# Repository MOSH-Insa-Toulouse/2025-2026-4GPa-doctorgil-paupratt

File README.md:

# 4A GP - Projet "Du capteur au banc de test" - I4PMH21

## Sommaire

* [Objectif du projet](#objectif-du-projet)
* [Philosophie du projet : Sobriété et Efficacité](#philosophie-du-projet--sobriété-et-efficacité)
* [Livrables](#livrables)
* [LTSpice](#ltspice)
* [KiCad](#kicad)
* [Shield](#shield)
* [Code Arduino](#code-arduino)
* [Application Android](#application-android)
* [Datasheet](#datasheet)
* [Conclusion et Bilan Critique](#conlcusion-et-bilan-critique)

---

## Objectif du projet

Dans le cadre d'un cours dispensé lors du 2<sup>nd</sup> semestre de 4<sup>ème</sup> année de Génie Physique à l'INSA de Toulouse, il nous a été proposé de réaliser un **capteur low-tech à base de graphite**, puis d'en faire une analyse critique argumentée pour en cerner les potentialités mais également pour évoquer des solutions d'amélioration. Ainsi, ce projet nous a permis de balayer l'ensemble du domaine ; du capteur jusqu'à la réalisation d'une **datasheet** et du **banc de test**.

---
## Philosophie du projet : Sobriété et Efficacité
Face à l'urgence climatique et à la demande croissante de systèmes à faible empreinte carbone, ce projet s'inscrit dans une démarche de **sobriété technologique**. Simplifier les composants pour les rendre plus efficaces énergétiquement reste un défi majeur de l'ingénierie moderne.

Si la réalisation de capteurs à haute sensibilité possède une forte valeur ajoutée, il est primordial de questionner nos besoins réels : avons-nous systématiquement besoin d'un capteur ultra-précis s'il consomme davantage ? Ou un capteur plus simple, adapté à l'usage final, est-il suffisant ?

Le choix d'un **capteur graphite "low-tech"** illustre ce compromis (trade-off) entre précision et consommation. Plutôt que de viser la performance absolue au prix d'une complexité accrue, nous avons privilégié une solution optimisée, cohérente avec les ressources disponibles et les exigences réelles du cahier des charges.

---

## Livrables

L'ensemble du projet comprend les éléments suivants :

* **Un shield PCB** branché à une board **Arduino UNO** sur lequel nous retrouverons différents composants tels que :
    * Un capteur graphite
    * Un circuit d'amplification transimpédance
    * Un module Bluetooth
    * Un encodeur rotatoire
    * Un potentiomètre digital (*qui vient remplacer la résistance R2 du circuit d'amplification*)
    * Un capteur de contrainte commercial
* **Une simulation LTSpice** du circuit transimpédance
* **Un fichier KiCad** du shield avec l'ensemble des composants cités en amont
* **Un code Arduino** qui gère le fonctionnement et les communications des modules avec la board
* **Un fichier APK Android** (conçue à l'aide du site *MIT APP Inventor*) qui permet, à partir d'un smartphone Android, de gérer l'interface avec le shield Arduino UNO par le biais d'une communication Bluetooth
* **La datasheet** du capteur graphite

> [!TIP]
> **Conseil de lecture** : Pour une compréhension optimale du projet, commencez par consulter la **Datasheet** qui résume les performances théoriques avant d'explorer les fichiers de conception KiCad.
---

## LTSpice

Afin de valider la faisabilité du projet et d'anticiper le comportement dynamique de notre système, nous avons simulé la chaîne de conditionnement sous LTSpice. Le défi majeur réside dans l'impédance extrêmement élevée du capteur (de l'ordre du $G\Omega$), qui génère des courants infimes, de l'ordre du nanoampère ($nA$). Pour rendre ce signal exploitable par un microcontrôleur, il est impératif de le filtrer contre les bruits parasites et de l'amplifier de manière significative. Le montage de transimpédance présenté ci-dessous remplit cette fonction critique :

*Circuit d'amplification/atténuation*

*Modélisation du capteur*

Ce montage se compose de trois filtres passe-bas distincts pour optimiser le rapport signal/bruit :

* **Premier étage ($R_5, C_1, R_1$)** : Filtre les bruits en courant sur le signal d'entrée induits par l'alimentation 5V (symbolisée par 'SINE' + $C_3$).
* **Deuxième étage ($C_4, R_3$)** : Réduit spécifiquement la composante de bruit à **50 Hz** induite par le réseau électrique ambiant.
* **Troisième étage ($R_6, C_2$)** : Placé en sortie de l'amplificateur, il atténue le bruit thermique et intrinsèque du circuit.

*Atténuation d'environ 46 dB à 50 Hz. Le comportement global du circuit est bel est bien passe-bas.*

Pour extraire la valeur de la résistance du capteur $R_c$ à partir de la tension mesurée $V_{adc}$, nous avons modélisé le circuit en régime statique (Basse Fréquence). 

En considérant l'AOP comme idéal en régime linéaire ($V_+ = V_-$) et en appliquant le théorème de **Millman**, nous obtenons les relations suivantes :

- #### Expression de $V_+$ (Diviseur de tension)
    $$V_+ = \frac{R_1}{R_c + R_1 + R_5} \cdot V_{cc}$$

- #### Expression de $V_-$ (Théorème de Millman)
    Comme l'entrée est reliée à la masse via $R_2$ :

    $$V_- = \frac{\frac{V_{out}}{R_3} + \frac{0}{R_2}}{\frac{1}{R_3} + \frac{1}{R_2}} = V_+$$

- #### Équation finale de la résistance $R_c$
    En posant $V_{out} = V_{adc}$ et en isolant $R_c$, nous arrivons à la formule de transfert utilisée dans le code Arduino :

    $$R_c = R_1 \cdot \frac{V_{cc}}{V_{adc}} \cdot \left(1 + \frac{R_3}{R_2}\right) - R_1 - R_5$$

Cette équation permet au microcontrôleur de convertir en temps réel la tension lue sur la broche analogique en une valeur de résistance physique exploitable pour la datasheet.

### Analyse des simulations et dimensionnement

La simulation nous a permis d'optimiser deux paramètres critiques : le filtrage du bruit secteur et la dynamique de mesure.

#### 1. Optimisation du filtrage (C4 et R3)
L'étude fréquentielle montre l'impact direct des composants sur la qualité du signal :
* **Fréquence de coupure** : Plus $C_4$ est petit, plus la fréquence de coupure $f_c = \frac{1}{2\pi R_3 C_4}$ est élevée, ce qui réduit l'efficacité du filtrage des parasites à **50 Hz**.
* **Gain du filtre** : La résistance $R_2$ permet d'ajuster le décalage vertical du signal pour l'adapter à la fenêtre de lecture.

*Simulation de l'influence de C4 et R3 sur la stabilisation du signal.*

#### 2. Stratégie de Calibration et Plage Dynamique
Pour éviter la saturation de l'ADC de l'Arduino (limité à 5V), nous avons conçu un système de réglage de gain flexible :

* **Problématique** : La résistance des capteurs graphite varie énormément selon le dépôt. Un courant $I_{sens}$ trop élevé peut saturer l'amplificateur à 5V, rendant toute variation de pression invisible.
* **Solution Manuelle** : L'utilisateur peut ajuster dynamiquement le gain via le **potentiomètre numérique** en utilisant l'**encodeur rotatif**. 
* **Objectif** : L'utilisateur tourne l'encodeur pour ramener le signal au repos vers **2,5V** (valeur brute de 512 sur l'ADC). Cela place le point de fonctionnement au milieu de l'échelle de mesure, offrant une marge de manœuvre maximale pour observer les variations sans écrêtage.

---
## KiCad

### Conception du Shield

Afin de concevoir un **shield PCB** conforme au cahier des charges de l'UF **I4PMH21**, nous avons développé un prototype virtuel sous **KiCad**. Cette phase de conception a permis d'intégrer l'ensemble des contraintes électroniques, mécaniques et physiques liées aux composants utilisés.

La première étape a consisté à élaborer la **saisie de schéma** (*schematic*) regroupant l'intégralité des modules :

### Routage du PCB (Layout)

Une fois le schéma validé, nous avons procédé au **routage du PCB**. L'enjeu principal a été la gestion de l'intégrité du signal dans un environnement mixte (analogique/numérique) :

* **Plan de masse** : Mise en place d'un plan de masse continu pour minimiser l'inductance de boucle et assurer une référence stable.
* **Isolation** : Séparation physique des pistes à haute impédance (liées au capteur graphite) pour limiter les couplages capacitifs.
* **Contraintes mécaniques** : Alignement des connecteurs pour un embrochage parfait sur l'Arduino UNO.

Pour maintenir l'intégrité du plan de masse et respecter les contraintes d'espace, nous avons opté pour la mise en place d'un **strap externe (jumper)**. Cette solution a permis de finaliser les connexions tout en garantissant une isolation optimale entre les pistes critiques.

Le design final du shield est présenté ci-dessous :

### Rendu 3D du Shield

Nous avons généré un rendu 3D du PCB pour visualiser l'encombrement final et l'agencement des composants. Voici une vue de dessus du projet :

> [!NOTE]
> **Ajustement des modèles 3D** : Vous remarquerez peut-être des chevauchements visuels sur le rendu. Cela s'explique par l'usage de modèles CAO (fichiers `.step`) standards dont l'encombrement diffère légèrement des composants réels soudés sur le banc de test. L'empreinte au sol (*footprint*) sur le cuivre est cependant parfaitement conforme aux composants physiques.

## Shield
Une fois la conception validée, nous avons procédé à la fabrication physique du shield sur une plaque d'époxy cuivrée à l'aide de Mme. Catherine Crouzet. Le processus de prototypage rapide a suivi les étapes classiques de la photogravure :

* **Insolation** : Transfert du typon (généré sous KiCad) sur la plaque photosensible via une exposition aux UV.

* **Révélation** : Élimination de la résine non exposée à l'aide d'un révélateur chimique.

* **Gravure** : Passage dans une solution de perchlorure de fer pour dissoudre le cuivre non protégé et révéler les pistes.

Après le nettoyage de la carte, nous avons procédé à l'assemblage. Cette étape a nécessité une grande précision, notamment pour le perçage des vias et le soudage des composants traversants (THT) et CMS, en veillant scrupuleusement au respect des contraintes de température pour ne pas endommager le capteur graphite.

> [!WARNING]
> **Points de vigilance (Soudure)** : Lors de l'assemblage, une attention extrême doit être portée à la qualité des soudures. Des micro-courts-circuits ou des contacts intermittents ("soudures sèches") ont été identifiés lors de nos tests initiaux, perturbant la stabilité du signal. Un nettoyage rigoureux et une vérification systématique au multimètre sont indispensables.

> [!NOTE]
> **Évolution du projet (Servomoteur)** : Bien que prévu initialement dans la conception du shield, le servomoteur n'a finalement pas été implémenté. Ce choix s'explique par des contraintes de temps et par le fait que le banc de test s'est révélé parfaitement fonctionnel et suffisant sans le servo pour valider les mesures du capteur.

## Code Arduino

En parallèle de la partie *KiCad*, nous avons développé le [Code Arduino](./Arduino/Code/ProjetMosh/ProjetMosh.ino) permettant la communication des composants avec l'**Arduino UNO**, voici les fonctionnalités principales :

* **Acquisition Analogique** : Lecture haute impédance et conversion du signal en résistance.
* **Contrôle du Gain via Encodeur** : Utilisation de l'**encodeur rotatif** pour incrémenter ou décrémenter la valeur du potentiomètre numérique. Cette interface permet à l'utilisateur de calibrer manuellement le capteur en temps réel.
* **Gestion du Potentiomètre Digital** : Communication via le bus I2C pour mettre à jour la résistance de contre-réaction ($R_2/R_g$) dès qu'une rotation de l'encodeur est détectée.
* **Interface Bluetooth** : Transmission des données vers l'application Android pour un monitoring sans fil.

> [!TIP]
> **Structure du code** : Le code est organisé de manière non-bloquante (utilisation de `millis()` au lieu de `delay()`) pour garantir une réactivité maximale de la liaison Bluetooth et de l'encodeur.

---

## Application Android
Nous avons réalisé une application mobile à l'aide de **MIT App Inventor**.  Ce dashboard permet non seulement de lire les valeurs du capteur graphite en temps réel, mais constitue également un outil d'acquisition de données complet.

> Le code de programmation est disponibles ici : **[Accéder au code de l'application](./Application/Code%20apk)**.

* **Liaison Bluetooth** : Connexion simplifiée avec le module HC-05 présent sur le shield.
* **Graphique Dynamique** : Visualisation temporelle de la résistance pour identifier la sensibilité du capteur à la déformation.

*Interface utilisateur pour la visualisation des données en temps réel.*

---
## Datasheet

La rédaction de la **datasheet** repose sur une série de mesures expérimentales effectuées grâce à un banc de test dédié.

Le banc de test, imprimé en 3D, utilise 7 demi-disques (Ø 1cm à 5cm) pour simuler des déformations contrôlées. Nous avons testé une gamme de capteurs allant du **2H au 3B** pour identifier le meilleur compromis entre conductivité initiale et sensibilité à la flexion.

*Classification des nuances de graphite : de la mine dure (H) à la mine tendre (B).*

*Montage complet*

 **Documentation technique** : Le rapport complet des performances est disponible ici : 
> 📄 **[Consulter la Datasheet (PDF)](./Caractérisation%20et%20Datasheet/Datasheet.pdf)**

> [!NOTE]
> **Sélection des échantillons** : Certains capteurs présentant des valeurs aberrantes ou une instabilité trop marquée ont été écartés de l'analyse finale afin de garantir la cohérence des courbes de tendance.

> [!WARNING]
> **Limites expérimentales** : La reproductibilité des mesures s'est avérée délicate. Plusieurs facteurs ont influencé les résultats :
> * **Variation de densité** du graphite lors du dépôt manuel.
> * **Dégradation mécanique** de la couche de graphite au fil des tests.
> * **Contacts électriques** instables en fin de série.

## Conclusion et Bilan Critique

Ce projet constitue une preuve de concept réussie : il démontre qu’un matériau aussi rudimentaire que le graphite déposé sur papier peut être transformé en un **capteur de déformation (strain sensor)** fonctionnel grâce à une chaîne de conditionnement électronique optimisée.

### Synthèse des résultats
Nos simulations et tests physiques ont validé la réponse piézorésistive attendue : la résistance augmente en extension et diminue en compression. Le système complet (Capteur -> Shield -> Arduino -> Android) est pleinement opérationnel pour du monitoring en temps réel.

Cependant, la reproductibilité demeure le principal défi technologique. L’hétérogénéité du dépôt manuel de graphite et les aléas liés au prototypage artisanal du PCB (gravure chimique, perçage et soudures) limitent la fiabilité des mesures.

### Perspectives : La force du Low-Tech
L'intérêt majeur de ce projet réside dans sa **valeur pédagogique**. Il prouve qu'un système d'instrumentation complet peut être conçu avec des ressources limitées. Plutôt que de complexifier le capteur, l'enjeu futur serait de rendre le processus de dépôt du graphite plus robuste et automatisé.

**En conclusion**, ce projet nous a permis d'appréhender l'ensemble du cycle de vie d'un produit électronique, de la physique fondamentale du capteur jusqu'à l'interface utilisateur mobile.

---
## Remerciements

Nous tenons à remercier Mme. Crouzet et M. Grisolia pour leur encadrement précieux et leurs conseils techniques lors de la phase de conception et de fabrication tout au long de ce projet.

---

## Contact

Si vous avez des questions concernant ce projet ou l'utilisation du shield, n'hésitez pas à nous contacter :

* **Oscar GIL** : [gil-lamassou@insa-toulouse.fr](mailto:gil-lamassou@insa-toulouse.fr)
* **Pau PRAT** : [prat-i-meler@insa-toulouse.fr](mailto:prat-i-meler@insa-toulouse.fr)

---

[↑ Retour au sommaire](#sommaire)

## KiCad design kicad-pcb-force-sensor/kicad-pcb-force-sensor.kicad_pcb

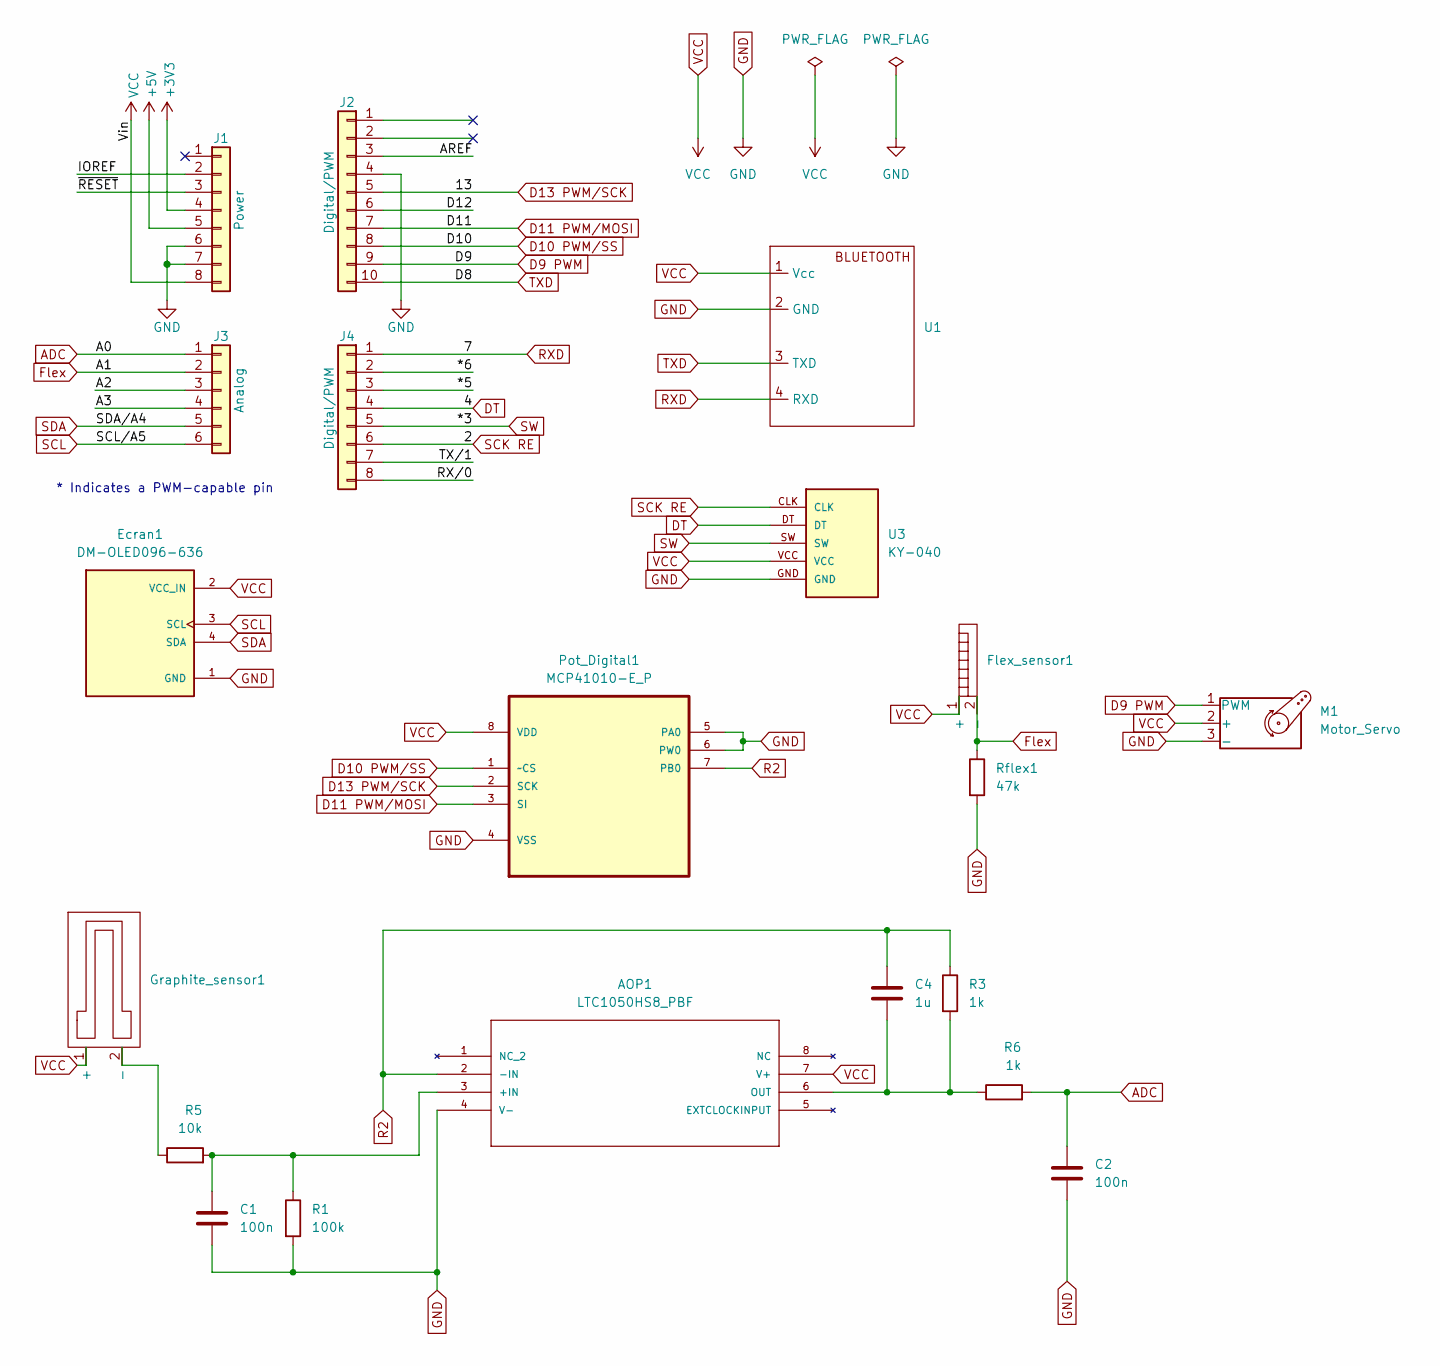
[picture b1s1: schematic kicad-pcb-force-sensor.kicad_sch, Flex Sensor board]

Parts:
AOP1: LTC1050HS8_PBF
C1, C2: 100n; C_Disc_D3.8mm_W2.6mm_P2.50mm
C4: 1u; C_Rect_L9.0mm_W2.5mm_P7.50mm_MKT
Ecran1: DM-OLED096-636; MODULE_DM-OLED096-636
Flex_sensor1: Flex
Graphite_sensor1: Graphite_sensor_emprunt
J1: Power; PinSocket_1x08_P2.54mm_Vertical
J2: Digital/PWM; PinSocket_1x10_P2.54mm_Vertical
J3: Analog; PinSocket_1x06_P2.54mm_Vertical
J4: Digital/PWM; PinSocket_1x08_P2.54mm_Vertical
M1: Motor_Servo; Servo
Pot_Digital1: MCP41010-E_P; MCP41010
R1: 100k; R_Axial_DIN0207_L6.3mm_D2.5mm_P15.24mm_Horizontal
R3, R6: 1k; R_Axial_DIN0204_L3.6mm_D1.6mm_P7.62mm_Horizontal
R5: 10k; R_Axial_DIN0207_L6.3mm_D2.5mm_P10.16mm_Horizontal
Rflex1: 47k; R_Axial_DIN0207_L6.3mm_D2.5mm_P10.16mm_Horizontal
U1: BT_HC05
U3: KY-040; KY-040-PORT

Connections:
+3V3: J1.4
+5V: J1.5
/*5: J4.3
/*6: J4.2
/A2: J3.3
/A3: J3.4
/AREF: J2.3
/D12: J2.6
/IOREF: J1.2
/RX/0: J4.8
/TX/1: J4.7
/~RESET: J1.3
ADC: C2.2, J3.1, R6.2
D9 PWM: J2.9, M1.1 (PWM)
D10 PWM/SS: J2.8, Pot_Digital1.1 (~CS)
D11 PWM/MOSI: J2.7, Pot_Digital1.3 (SI)
D13 PWM/SCK: J2.5, Pot_Digital1.2 (SCK)
DT: J4.4, U3.DT
Flex: Flex_sensor1.2 (-), J3.2, Rflex1.1
GND: AOP1.4 (V-), C1.1, C2.1, Ecran1.1 (GND), J1.6, J1.7, J2.4, M1.3 (-), Pot_Digital1.4 (VSS), Pot_Digital1.5 (PA0), Pot_Digital1.6 (PW0), R1.2, Rflex1.2, U1.2 (GND), U3.GND
unnamed: AOP1.3 (+IN), C1.2, R1.1, R5.2
unnamed: AOP1.6 (OUT), C4.1, R3.2, R6.1
unnamed: Graphite_sensor1.2 (-), R5.1
R2: AOP1.2 (-IN), C4.2, Pot_Digital1.7 (PB0), R3.1
RXD: J4.1, U1.4 (RXD)
SCK RE: J4.6, U3.CLK
SCL: Ecran1.3 (SCL), J3.6
SDA: Ecran1.4 (SDA), J3.5
SW: J4.5, U3.SW
TXD: J2.10, U1.3 (TXD)
VCC: AOP1.7 (V+), Ecran1.2 (VCC_IN), Flex_sensor1.1 (+), Graphite_sensor1.1 (+), J1.8, M1.2 (+), Pot_Digital1.8 (VDD), U1.1 (Vcc), U3.VCC

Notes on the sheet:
* Indicates a PWM-capable pin

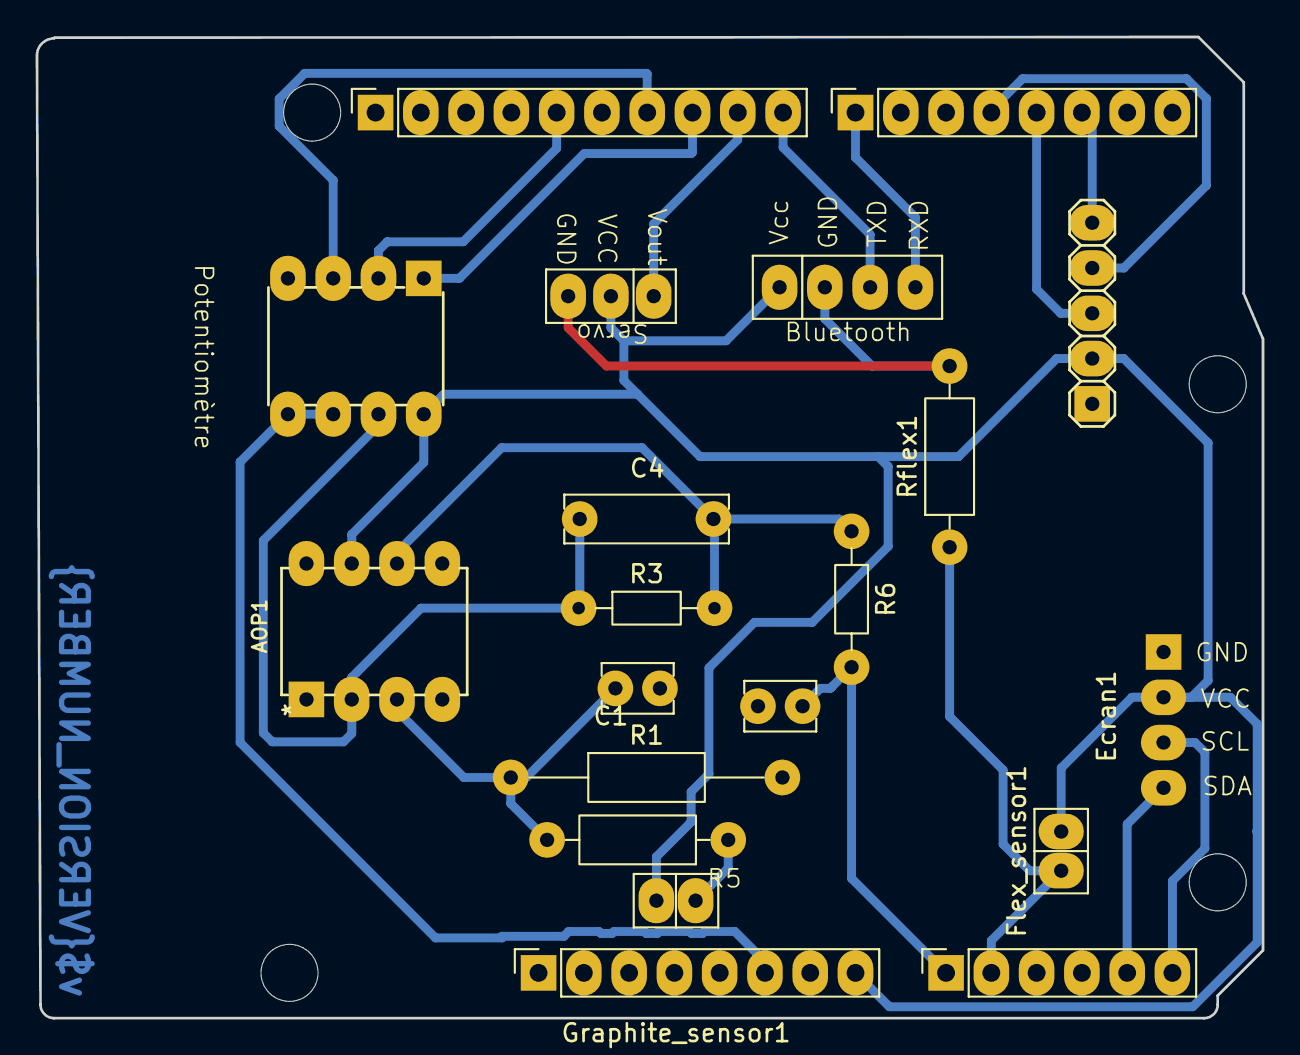
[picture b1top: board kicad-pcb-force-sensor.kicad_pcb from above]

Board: 2 copper layers, 68.8 x 55.0 mm, 24 parts (0 on the bottom side), 19 nets.

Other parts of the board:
MH1, MH2, MH3, MH4: MountingHole_3.2mm

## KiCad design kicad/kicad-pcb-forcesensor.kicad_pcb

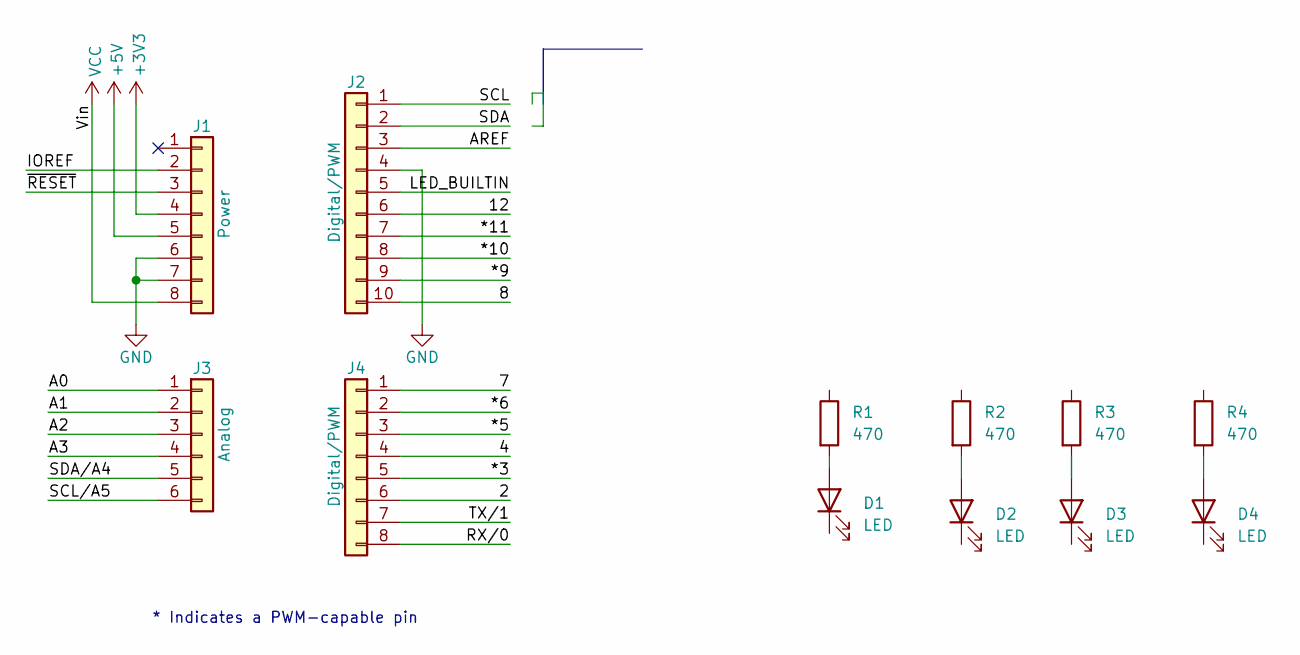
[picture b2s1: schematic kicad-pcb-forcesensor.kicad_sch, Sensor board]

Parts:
D1, D2, D3, D4: LED; LED_D5.0mm
J1: Power; PinSocket_1x08_P2.54mm_Vertical
J2: Digital/PWM; PinSocket_1x10_P2.54mm_Vertical
J3: Analog; PinSocket_1x06_P2.54mm_Vertical
J4: Digital/PWM; PinSocket_1x08_P2.54mm_Vertical
R1, R2, R3, R4: 470; R_Axial_DIN0207_L6.3mm_D2.5mm_P10.16mm_Horizontal

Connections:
+3V3: J1.4
+5V: J1.5
/2: J4.6
/4: J4.4
/7: J4.1
/8: J2.10
/12: J2.6
/*3: J4.5
/*5: J4.3
/*6: J4.2
/*9: J2.9
/*10: J2.8
/*11: J2.7
/A0: J3.1
/A1: J3.2
/A2: J3.3
/A3: J3.4
/AREF: J2.3
/IOREF: J1.2
/LED_BUILTIN: J2.5
/RX/0: J4.8
/SCL: J2.1
/SCL/A5: J3.6
/SDA: J2.2
/SDA/A4: J3.5
/TX/1: J4.7
/~RESET: J1.3
GND: J1.6, J1.7, J2.4
unnamed: D1.2 (A), R1.2
unnamed: D2.2 (A), R2.2
unnamed: D3.2 (A), R3.2
unnamed: D4.2 (A), R4.2
VCC: J1.8

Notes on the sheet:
* Indicates a PWM-capable pin

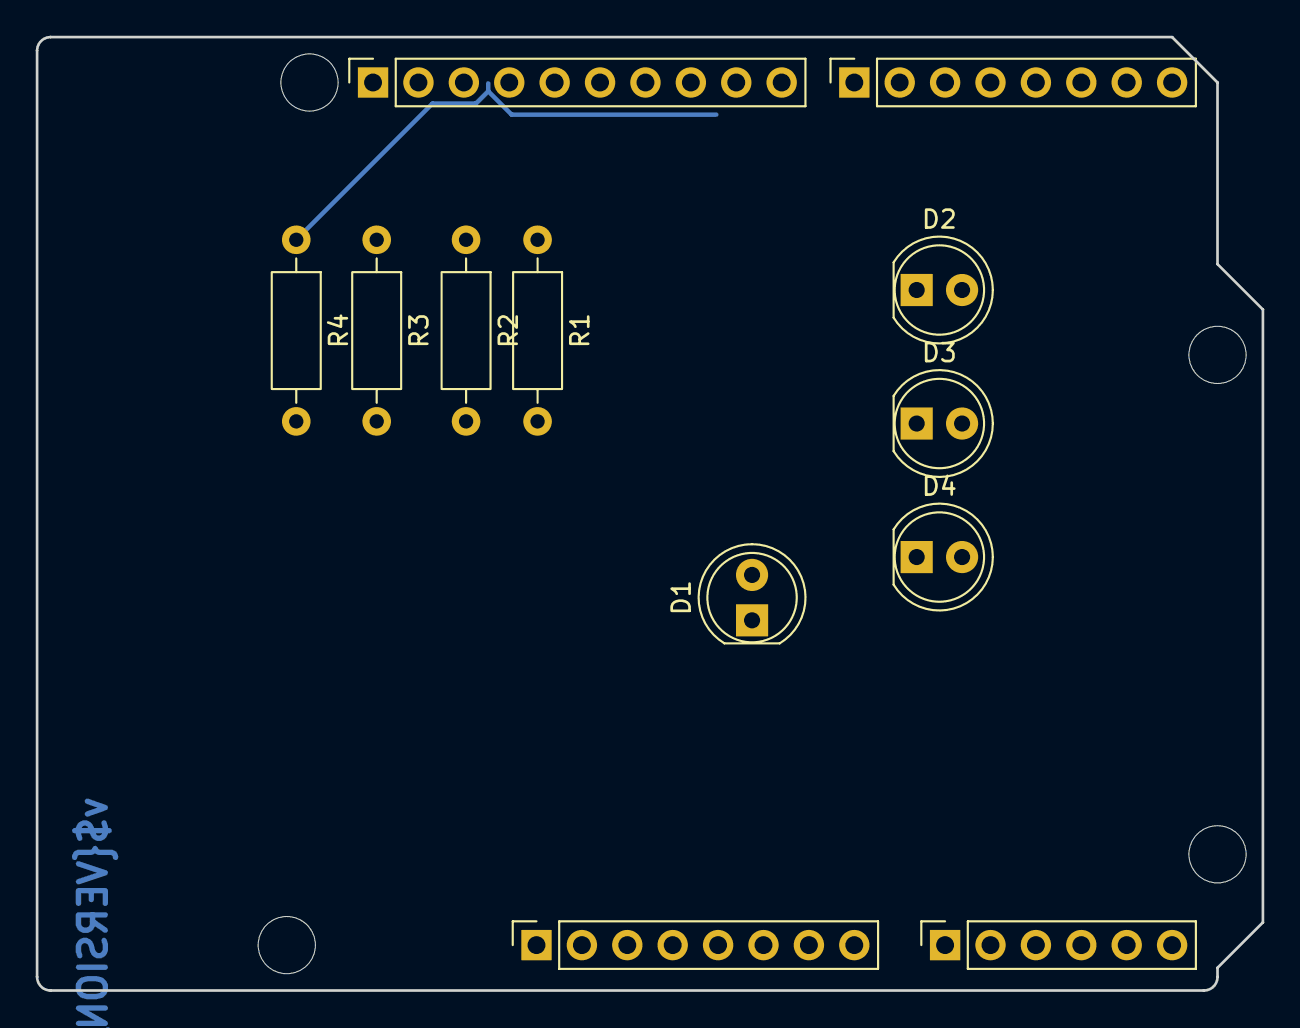
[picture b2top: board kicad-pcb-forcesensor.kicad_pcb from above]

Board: 2 copper layers, 68.6 x 53.3 mm, 16 parts (0 on the bottom side), 5 nets.

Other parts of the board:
MH1, MH2, MH3, MH4: MountingHole_3.2mm

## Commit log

2026-02-18 Ajout du projet KICAD
2026-02-18 Cambio de pin prueba
2026-02-18 prueba
2026-02-18 tamere
2026-02-18 Pines graphic sesor
2026-02-18 ground
2026-02-18 flex_sensor
2026-02-18 prueba2
2026-02-18 Servo
2026-02-18 Ground y VCC
2026-02-18 Avec pistes
2026-02-25 Modifier pins à 0.8mm plus détails
2026-03-10 GND y pins header arduino
2026-04-11 Code Arduino + Primera modificación codigo readme
2026-04-11 update readme 1
2026-04-11 update readme 2
2026-04-11 Update readme partie LTSpice
2026-04-11 Tips
2026-04-11 tips 1
2026-04-13 partie Kicad
2026-04-13 shield
2026-04-13 note évolution du projet servomoteur
2026-04-13 iamge
2026-04-15 Caractérisation et datasheet
2026-04-15 move readme
2026-04-16 readme
2026-04-16 Images
2026-04-16 code
2026-04-16 code 1
2026-04-16 Code3
2026-04-16 Image
2026-04-16 forma
2026-04-17 datasheet
2026-04-17 datasheet v2
2026-04-17 kicad malo borrado
2026-04-17 Datasheet 3
2026-04-17 Conclusion
2026-04-18 nueva datasheet
2026-04-18 remerciements et contacts
